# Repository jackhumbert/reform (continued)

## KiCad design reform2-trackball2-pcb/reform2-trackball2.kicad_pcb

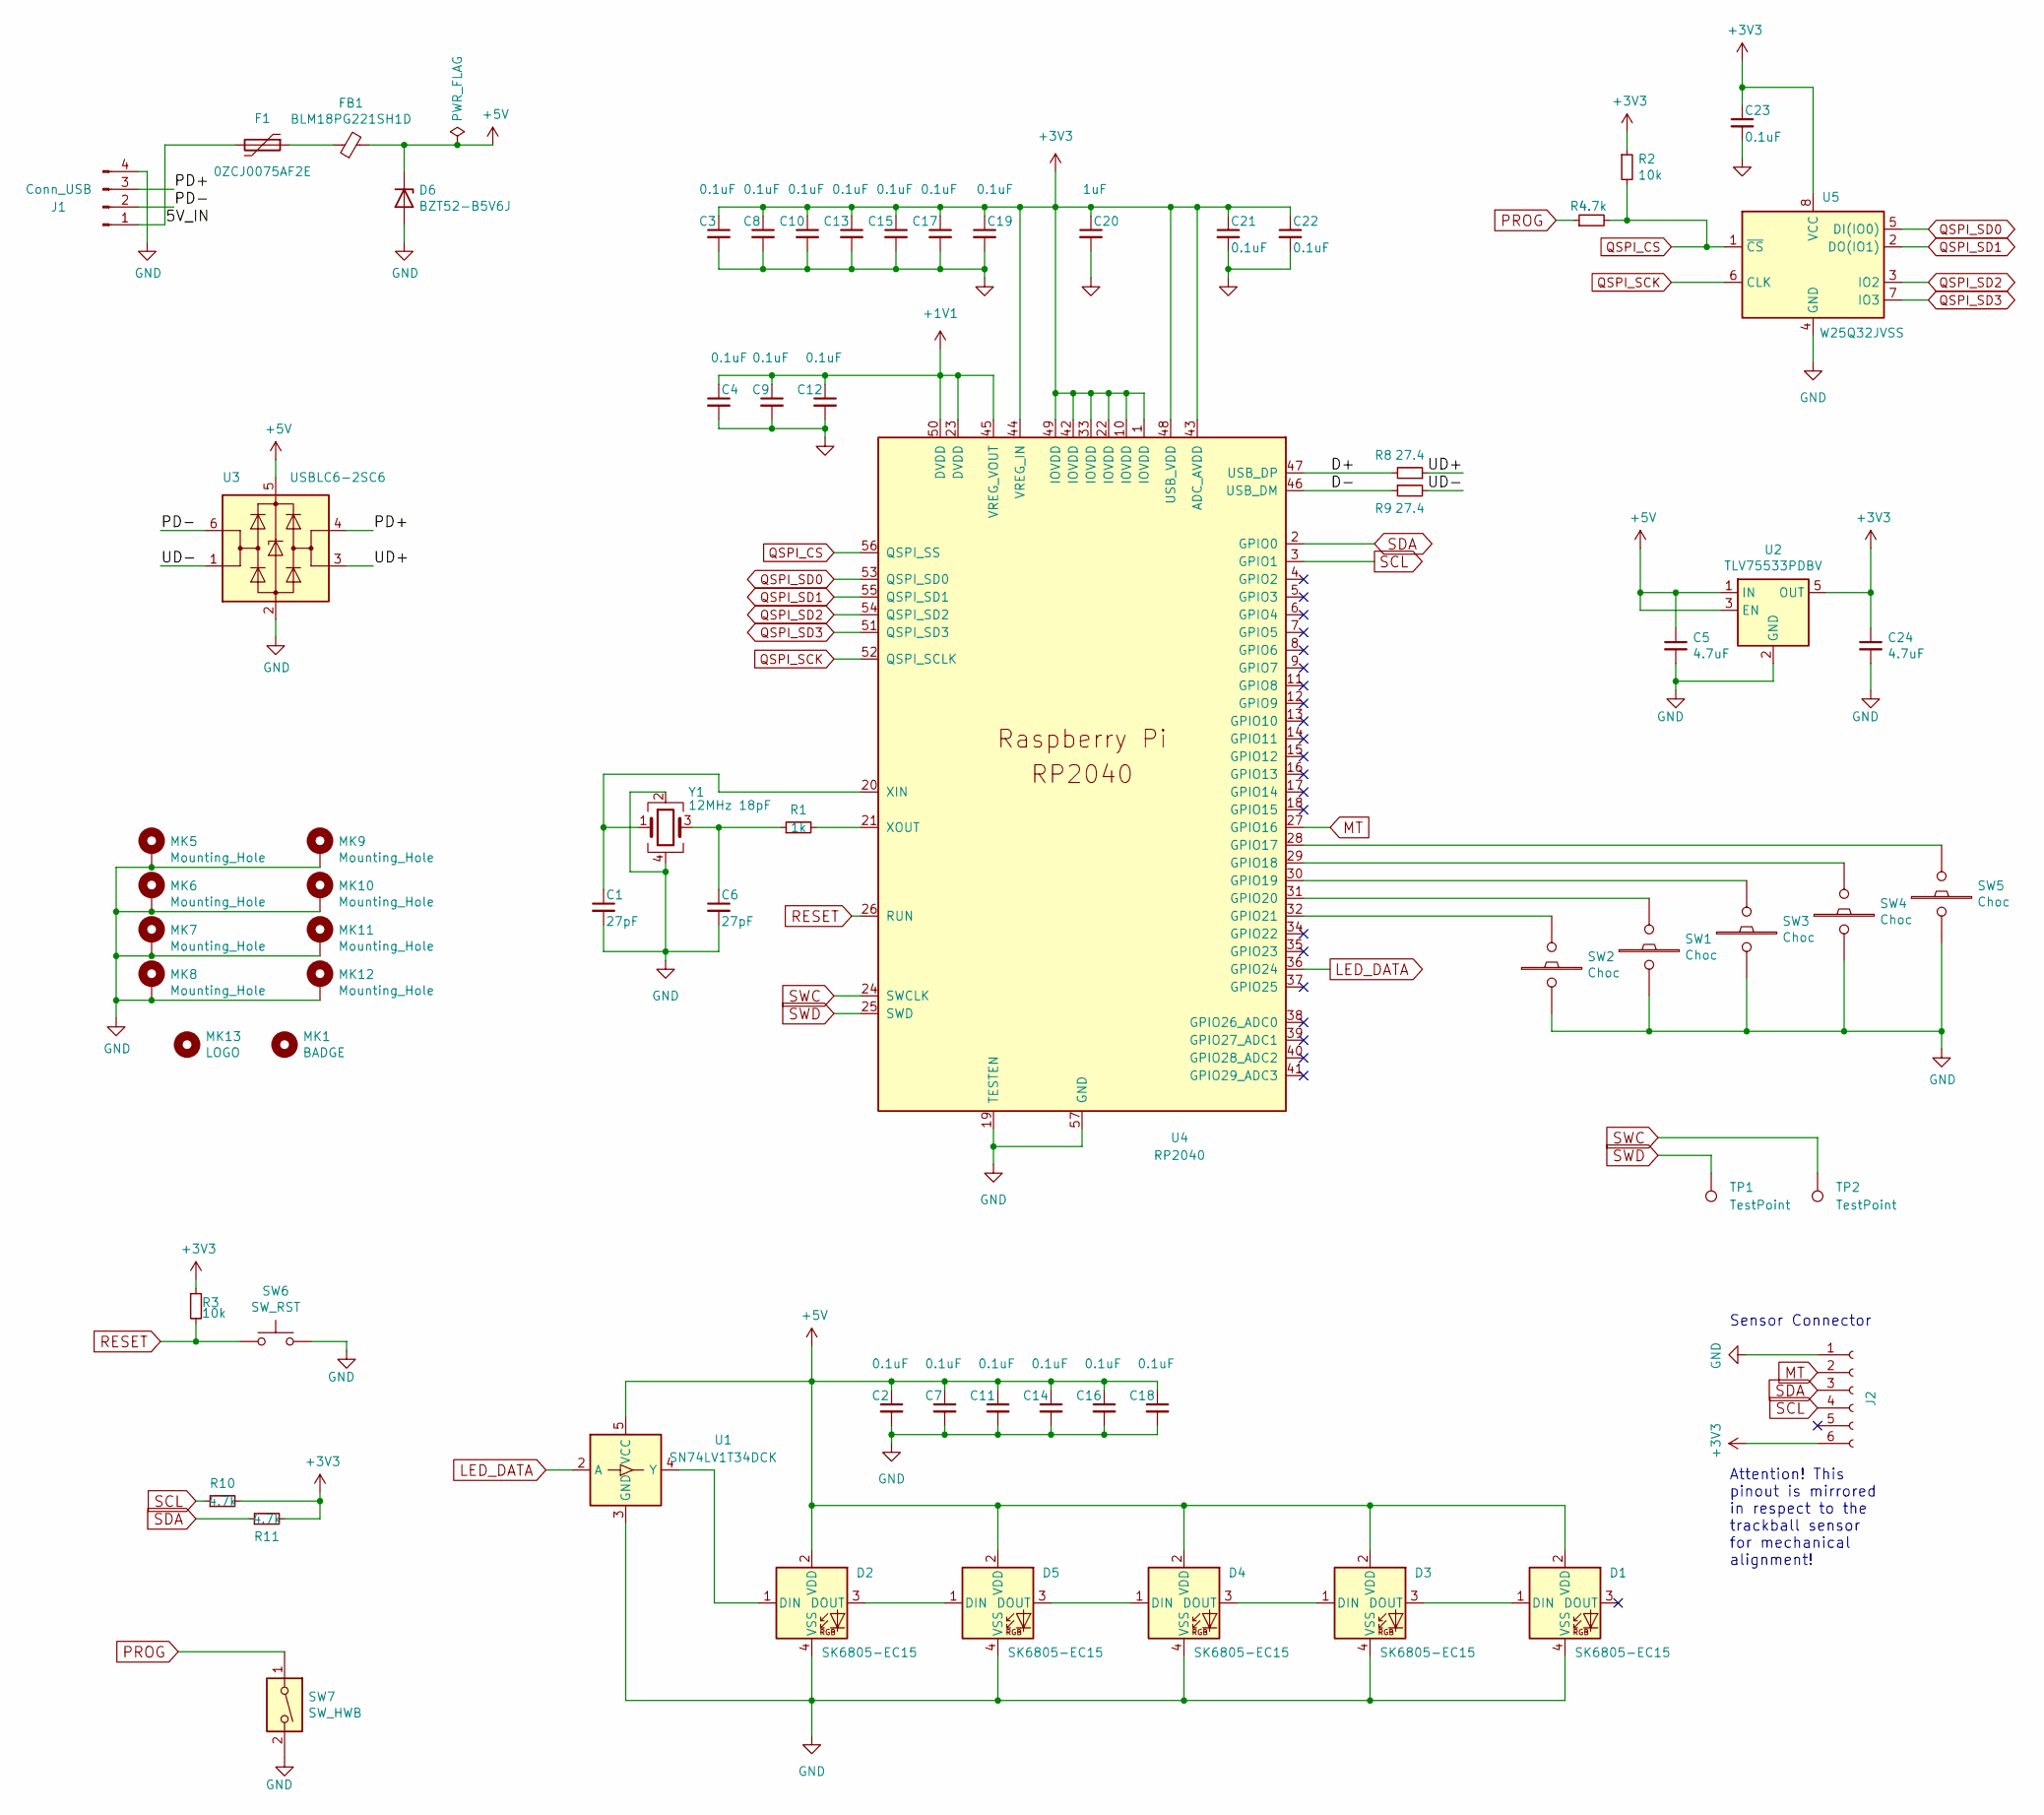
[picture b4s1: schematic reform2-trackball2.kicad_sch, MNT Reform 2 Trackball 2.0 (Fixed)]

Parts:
C1, C6: 27pF; C_0603_1608Metric; LCSC C107045
C2, C3, C4, C7, C8, C9, C10, C11, C12, C13, C14, C15, C16, C17, C18, C19, C21, C22, C23: 0.1uF; C_0603_1608Metric; LCSC C14663
C5, C24: 4.7uF; C_0603_1608Metric; LCSC C90057
C20: 1uF; C_0603_1608Metric; LCSC C14664
D1, D2, D3, D4, D5: SK6805-EC15; LCSC C2890035
D6: BZT52-B5V6J; D_SOD-123; LCSC C173406
F1: 0ZCJ0075AF2E; Fuse_1206_3216Metric_Castellated; LCSC C70082
FB1: BLM18PG221SH1D; L_0603_1608Metric; LCSC C14709
J1: Conn_USB; JST_PH_B4B-PH-K_1x04_P2.00mm_Vertical; LCSC C131334
J2: Conn_01x06_Female; Hirose_FH12-6S-0.5SH_1x06-1MP_P0.50mm_Horizontal; LCSC C202118
MK1: BADGE; mntreform-trackball-badge; LCSC DNP
MK5, MK6, MK7, MK8, MK9, MK10, MK11, MK12: Mounting_Hole; MountingHole_2.2mm_M2_Pad; LCSC DNP
MK13: LOGO; mntreform; LCSC DNP
R1: 1k; R_0603_1608Metric
R2, R3: 10k; R_0603_1608Metric; LCSC C99198
R4, R10, R11: 4.7k; R_0603_1608Metric; LCSC C105428
R8, R9: 27.4; R_0603_1608Metric; LCSC C185346
SW1, SW2, SW3, SW4, SW5: Choc; PG1350; LCSC C400231
SW6: SW_RST; Diptronics-PTLP2; LCSC C318893
SW7: SW_HWB; SW_DIP_SPSTx01_Slide_Omron_A6S-110x_W8.9mm_P2.54mm; LCSC C402914
TP1, TP2: TestPoint; TestPoint_Pad_D1.0mm; LCSC DNP
U1: SN74LV1T34DCK; SOT-353_SC-70-5; LCSC C78541
U2: TLV75533PDBV; SOT-23-5; LCSC C404027
U3: USBLC6-2SC6; SOT-23-6; LCSC C7519
U4: RP2040; RP2040-QFN-56; LCSC C2040
U5: W25Q32JVSS; SOIC-8_5.23x5.23mm_P1.27mm; LCSC C82344
Y1: 12MHz 18pF; Crystal_SMD_3225-4Pin_3.2x2.5mm; LCSC C91749

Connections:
+1V1: C4.1, C9.1, C12.1, U4.23 (DVDD), U4.45 (VREG_VOUT), U4.50 (DVDD)
/5V_IN: F1.2, J1.1
/D+: R8.2, U4.47 (USB_DP)
/D-: R9.1, U4.46 (USB_DM)
/PD+: J1.3, U3.4 (I/O2)
/PD-: J1.2, U3.6 (I/O1)
/UD+: R8.1, U3.3 (I/O2)
/UD-: R9.2, U3.1 (I/O1)
LED_DATA: U1.2 (A), U4.36 (GPIO24)
MT: J2.2, U4.27 (GPIO16)
unnamed: C1.1, U4.20 (XIN), Y1.1
unnamed: C6.1, R1.1, Y1.3
unnamed: D1.1 (DIN), D3.3 (DOUT)
unnamed: D2.1 (DIN), U1.4 (Y)
unnamed: D2.3 (DOUT), D5.1 (DIN)
unnamed: D3.1 (DIN), D4.3 (DOUT)
unnamed: D4.1 (DIN), D5.3 (DOUT)
unnamed: F1.1, FB1.1
unnamed: R1.2, U4.21 (XOUT)
unnamed: SW1.1, U4.31 (GPIO20)
unnamed: SW2.1, U4.32 (GPIO21)
unnamed: SW3.1, U4.30 (GPIO19)
unnamed: SW4.1, U4.29 (GPIO18)
unnamed: SW5.1, U4.28 (GPIO17)
PROG: R4.1, SW7.1
QSPI_CS: R2.2, R4.2, U4.56 (QSPI_SS), U5.1 (~CS)
QSPI_SCK: U4.52 (QSPI_SCLK), U5.6 (CLK)
QSPI_SD0: U4.53 (QSPI_SD0), U5.5 (DI(IO0))
QSPI_SD1: U4.55 (QSPI_SD1), U5.2 (DO(IO1))
QSPI_SD2: U4.54 (QSPI_SD2), U5.3 (IO2)
QSPI_SD3: U4.51 (QSPI_SD3), U5.7 (IO3)
RESET: R3.2, SW6.1, U4.26 (RUN)
SCL: J2.4, R10.1, U4.3 (GPIO1)
SDA: J2.3, R11.1, U4.2 (GPIO0)
SWC: TP2.1, U4.24 (SWCLK)
SWD: TP1.1, U4.25 (SWD)

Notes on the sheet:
Sensor Connector
Attention! This pinout is mirrored in respect to the trackball sensor for mechanical alignment!

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
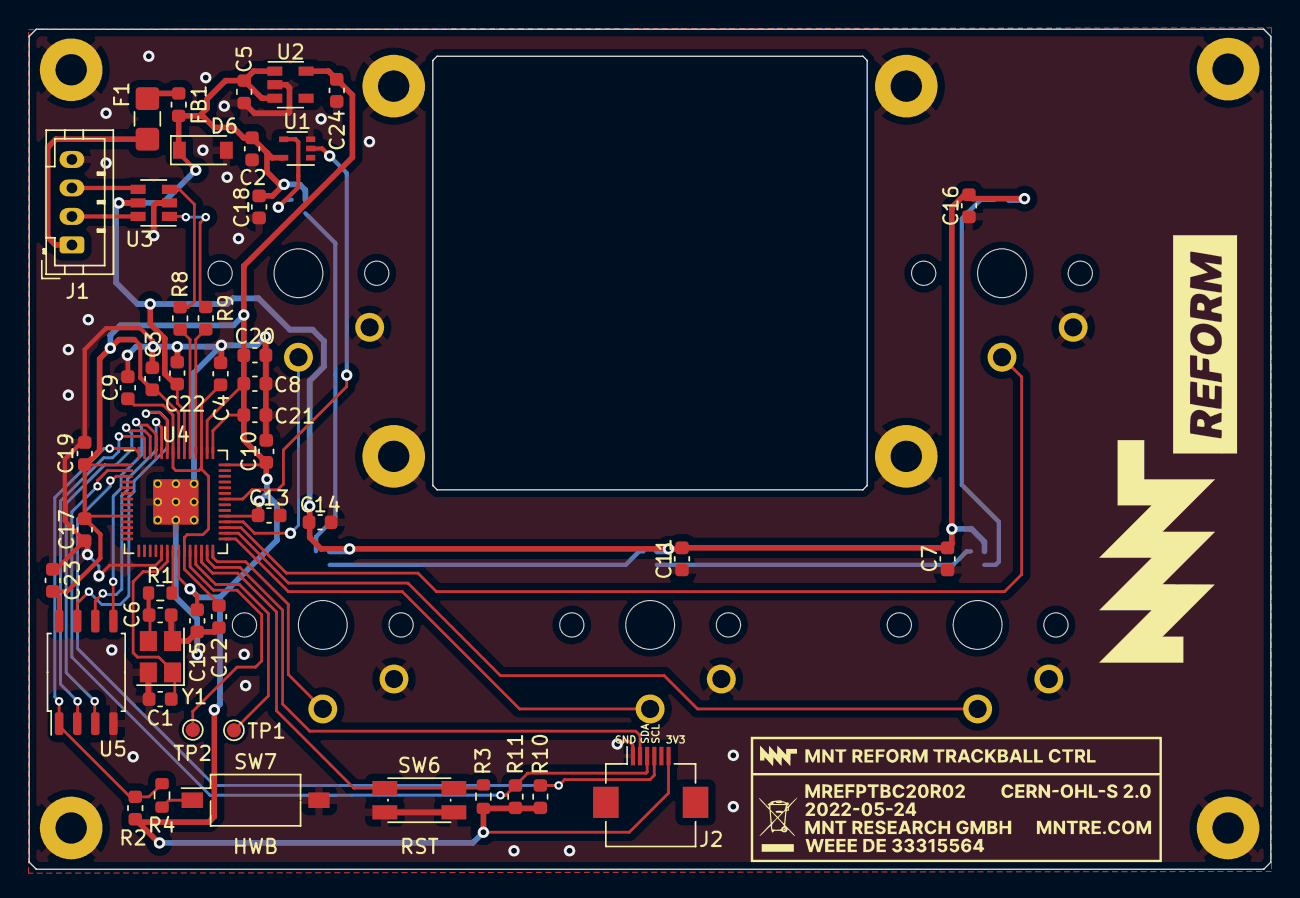
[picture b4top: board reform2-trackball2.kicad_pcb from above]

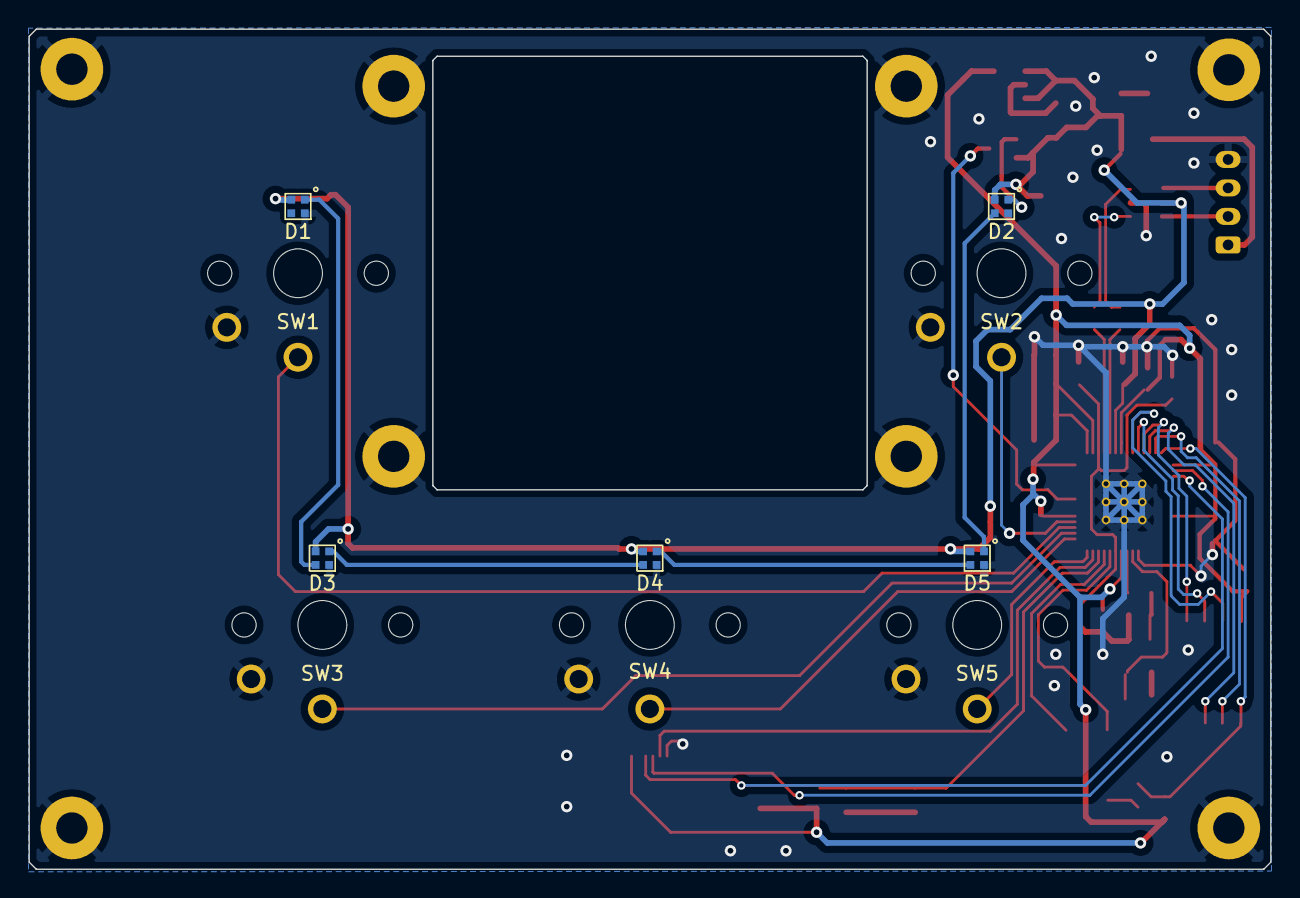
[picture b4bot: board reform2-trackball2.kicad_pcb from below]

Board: 2 copper layers, 87.2 x 59.0 mm, 67 parts (10 on the bottom side), 39 nets.

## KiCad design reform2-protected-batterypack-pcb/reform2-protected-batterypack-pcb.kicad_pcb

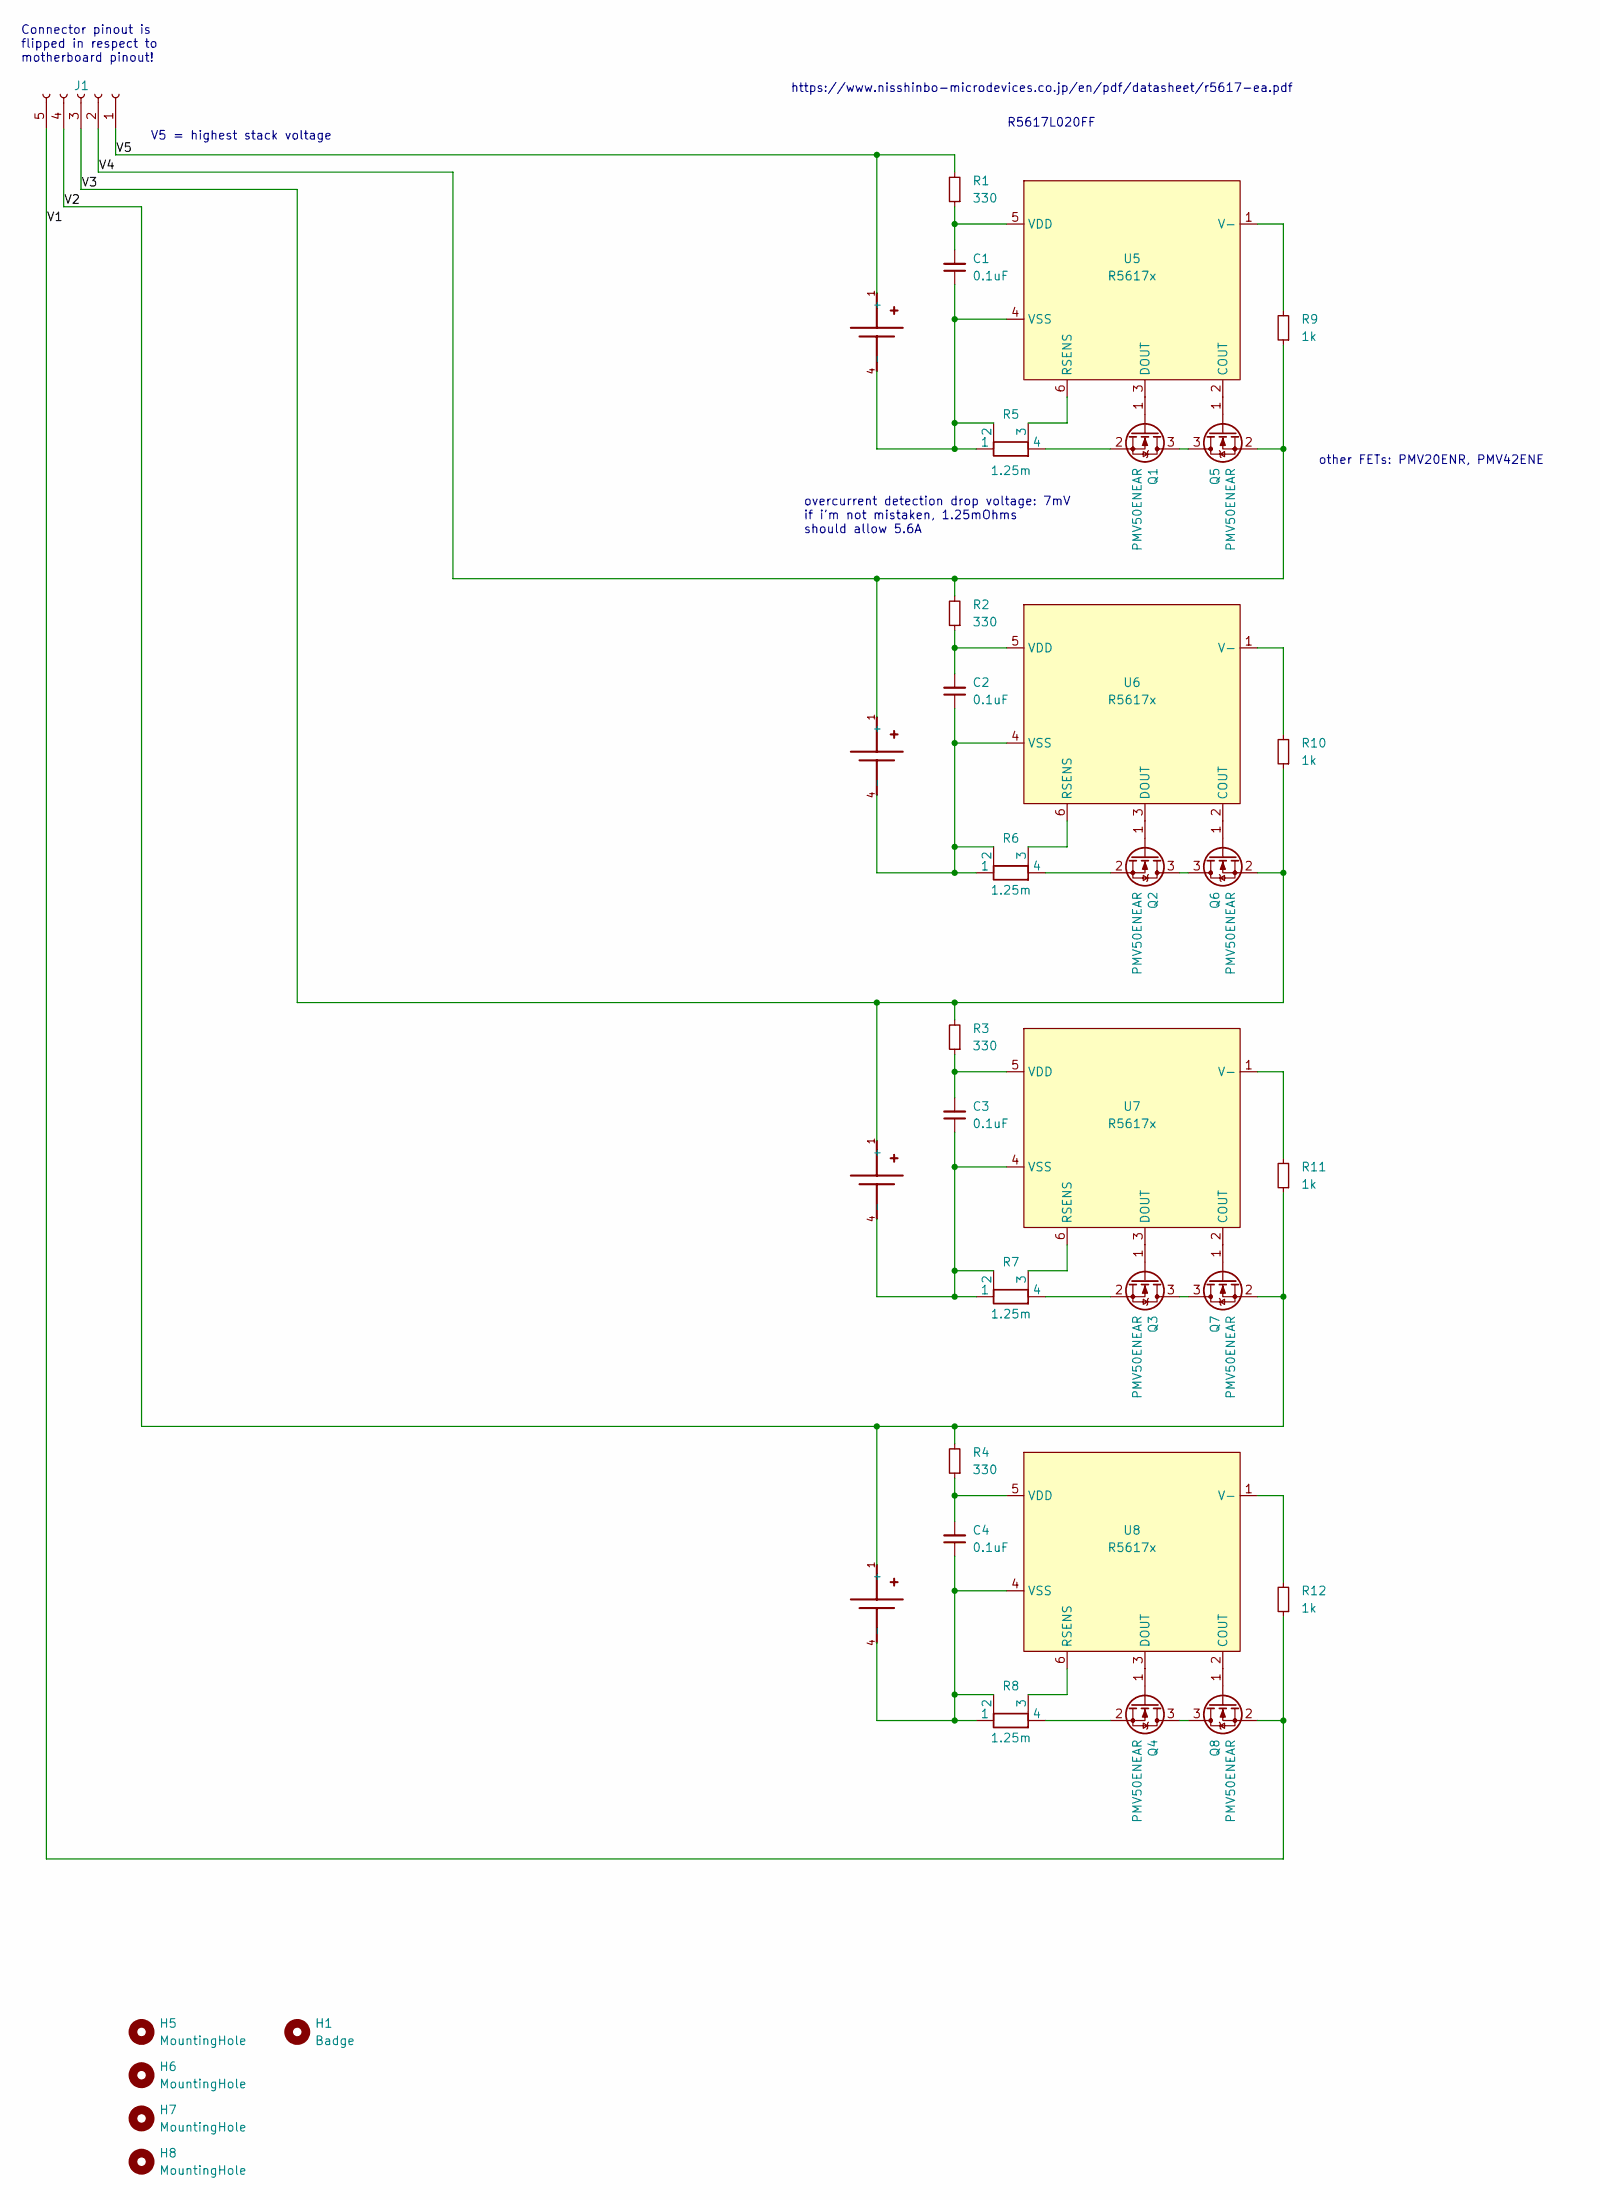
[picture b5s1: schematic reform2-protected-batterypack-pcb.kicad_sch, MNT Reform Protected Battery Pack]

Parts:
C1, C2, C3, C4: 0.1uF; C_0603_1608Metric
H1: Badge; mref-protected-batterypack-badge
H5, H6, H7, H8: MountingHole; MountingHole_2.2mm_M2
J1: Conn_01x05_Female; Molex_Pico-Lock_504050-0591_1x05-1MP_P1.50mm_Horizontal
Q1, Q2, Q3, Q4, Q5, Q6, Q7, Q8: PMV50ENEAR; SOT-23
R1, R2, R3, R4: 330; R_0603_1608Metric
R5, R6, R7, R8: 1.25m; R_1206_3216Metric_Kelvin
R9, R10, R11, R12: 1k; R_0603_1608Metric
U1, U2, U3, U4: KEYSTONE_54; Keystone54
U5, U6, U7, U8: R5617x; DFN-R5617_P0.5mm

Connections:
/V1: J1.5, Q8.2 (S), R12.1
/V2: J1.4, Q7.2 (S), R4.2, R11.1, U4.1 (+), U4.2 (+), U4.3 (+)
/V3: J1.3, Q6.2 (S), R3.2, R10.1, U3.1 (+), U3.2 (+), U3.3 (+)
/V4: J1.2, Q5.2 (S), R2.2, R9.1, U2.1 (+), U2.2 (+), U2.3 (+)
/V5: J1.1, R1.2, U1.1 (+), U1.2 (+), U1.3 (+)
unnamed: C1.1, R5.1, R5.2, U1.4 (-), U1.5 (-), U1.6 (-), U5.4 (VSS)
unnamed: C1.2, R1.1, U5.5 (VDD)
unnamed: C2.1, R6.1, R6.2, U2.4 (-), U2.5 (-), U2.6 (-), U6.4 (VSS)
unnamed: C2.2, R2.1, U6.5 (VDD)
unnamed: C3.1, R7.1, R7.2, U3.4 (-), U3.5 (-), U3.6 (-), U7.4 (VSS)
unnamed: C3.2, R3.1, U7.5 (VDD)
unnamed: C4.1, R8.1, R8.2, U4.4 (-), U4.5 (-), U4.6 (-), U8.4 (VSS)
unnamed: C4.2, R4.1, U8.5 (VDD)
unnamed: Q1.1 (G), U5.3 (DOUT)
unnamed: Q1.2 (S), R5.4
unnamed: Q1.3 (D), Q5.3 (D)
unnamed: Q2.1 (G), U6.3 (DOUT)
unnamed: Q2.2 (S), R6.4
unnamed: Q2.3 (D), Q6.3 (D)
unnamed: Q3.1 (G), U7.3 (DOUT)
unnamed: Q3.2 (S), R7.4
unnamed: Q3.3 (D), Q7.3 (D)
unnamed: Q4.1 (G), U8.3 (DOUT)
unnamed: Q4.2 (S), R8.4
unnamed: Q4.3 (D), Q8.3 (D)
unnamed: Q5.1 (G), U5.2 (COUT)
unnamed: Q6.1 (G), U6.2 (COUT)
unnamed: Q7.1 (G), U7.2 (COUT)
unnamed: Q8.1 (G), U8.2 (COUT)
unnamed: R6.3, U6.6 (RSENS)
unnamed: R7.3, U7.6 (RSENS)
unnamed: R8.3, U8.6 (RSENS)
unnamed: R9.2, U5.1 (V-)
unnamed: R10.2, U6.1 (V-)
unnamed: R11.2, U7.1 (V-)
unnamed: R12.2, U8.1 (V-)
unnamed: R5.3, U5.6 (RSENS)

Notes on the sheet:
other FETs: PMV20ENR, PMV42ENE
overcurrent detection drop voltage: 7mV if i'm not mistaken, 1.25mOhms should allow 5.6A
R5617L020FF
https://www.nisshinbo-microdevices.co.jp/en/pdf/datasheet/r5617-ea.pdf
V5 = highest stack voltage
Connector pinout is flipped in respect to motherboard pinout!

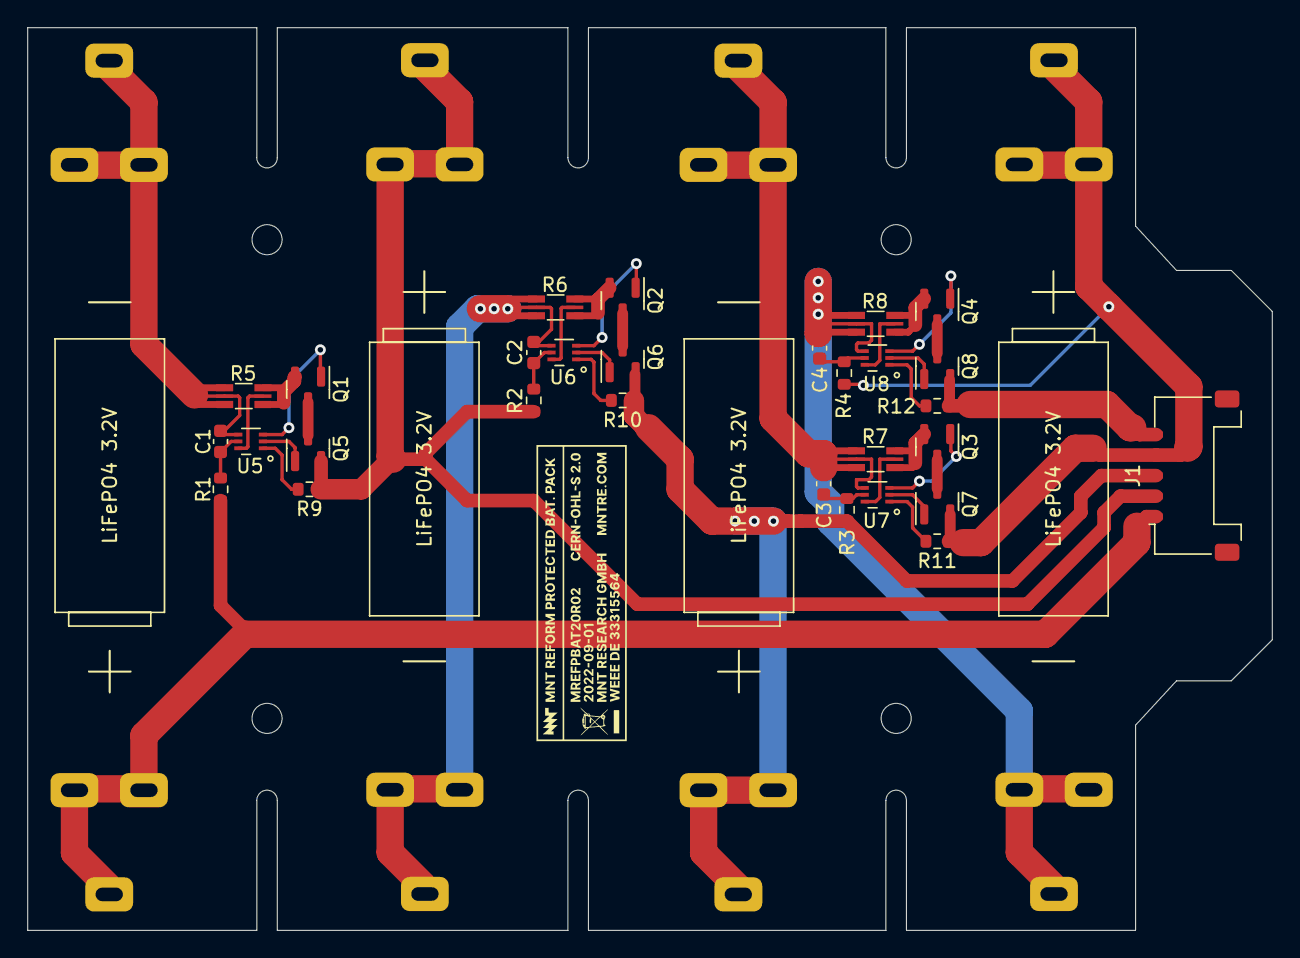
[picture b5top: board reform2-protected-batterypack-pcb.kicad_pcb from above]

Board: 2 copper layers, 91.0 x 66.0 mm, 38 parts (0 on the bottom side), 37 nets.

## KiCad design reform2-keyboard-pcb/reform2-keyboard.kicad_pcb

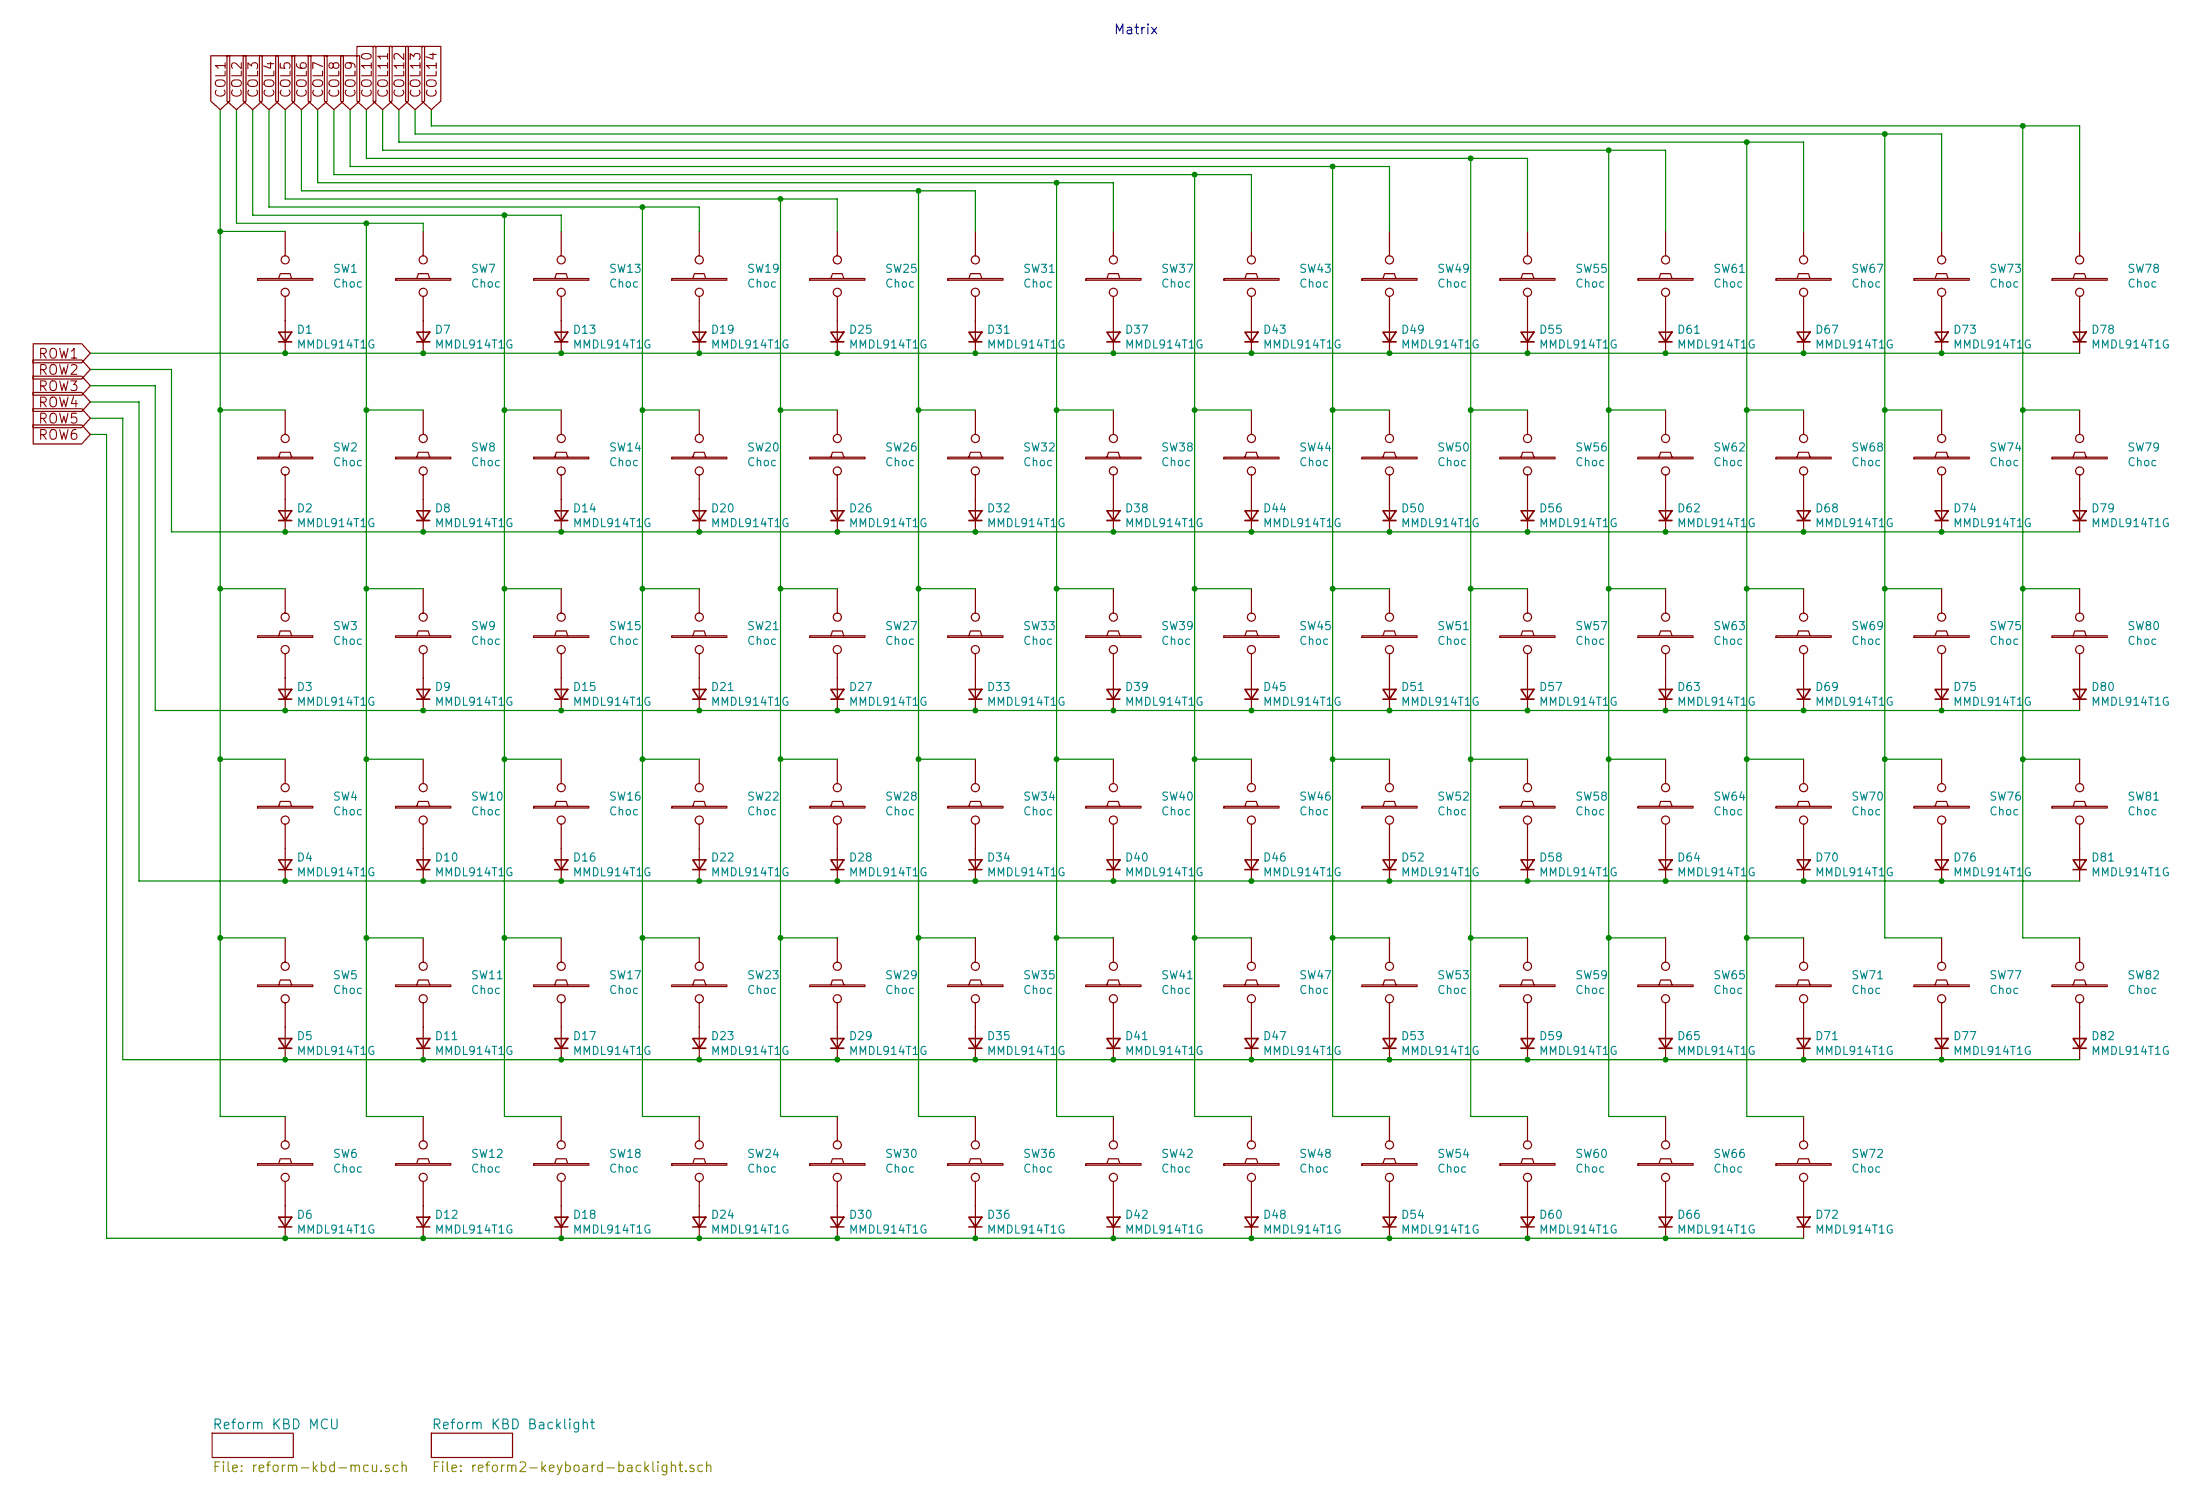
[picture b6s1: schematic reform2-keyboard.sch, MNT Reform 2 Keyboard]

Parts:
D1, D2, D3, D4, D5, D6, D7, D8, D9, D10, D11, D12, D13, D14, D15, D16, D17, D18, D19, D20, D21, D22, D23, D24, D25, D26, D27, D28, D29, D30, D31, D32, D33, D34, D35, D36, D37, D38, D39, D40, D41, D42, D43, D44, D45, D46, D47, D48, D49, D50, D51, D52, D53, D54, D55, D56, D57, D58, D59, D60, D61, D62, D63, D64, D65, D66, D67, D68, D69, D70, D71, D72, D73, D74, D75, D76, D77, D78, D79, D80, D81, D82: MMDL914T1G; D_0603_1608Metric_Pad1.05x0.95mm_HandSolder
SW1, SW2, SW3, SW4, SW5, SW6, SW7, SW8, SW9, SW10, SW11, SW12, SW13, SW14, SW15, SW16, SW17, SW18, SW19, SW20, SW21, SW22, SW23, SW24, SW25, SW26, SW27, SW28, SW29, SW30, SW31, SW32, SW33, SW34, SW35, SW36, SW37, SW38, SW39, SW40, SW41, SW42, SW43, SW44, SW45, SW46, SW47, SW48, SW49, SW50, SW51, SW52, SW53, SW54, SW55, SW56, SW57, SW58, SW59, SW60, SW61, SW62, SW63, SW64, SW65, SW66, SW67, SW68, SW69, SW70, SW71, SW72, SW73, SW74, SW75, SW76, SW77, SW78, SW79, SW80, SW81, SW82: Choc; PG1350

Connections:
COL1: SW1.1, SW2.1, SW3.1, SW4.1, SW5.1, SW6.1; also elsewhere on the board
COL2: SW7.1, SW8.1, SW9.1, SW10.1, SW11.1, SW12.1; also elsewhere on the board
COL3: SW13.1, SW14.1, SW15.1, SW16.1, SW17.1, SW18.1; also elsewhere on the board
COL4: SW19.1, SW20.1, SW21.1, SW22.1, SW23.1, SW24.1; also elsewhere on the board
COL5: SW25.1, SW26.1, SW27.1, SW28.1, SW29.1, SW30.1; also elsewhere on the board
COL6: SW31.1, SW32.1, SW33.1, SW34.1, SW35.1, SW36.1; also elsewhere on the board
COL7: SW37.1, SW38.1, SW39.1, SW40.1, SW41.1, SW42.1; also elsewhere on the board
COL8: SW43.1, SW44.1, SW45.1, SW46.1, SW47.1, SW48.1; also elsewhere on the board
COL9: SW49.1, SW50.1, SW51.1, SW52.1, SW53.1, SW54.1; also elsewhere on the board
COL10: SW55.1, SW56.1, SW57.1, SW58.1, SW59.1, SW60.1; also elsewhere on the board
COL11: SW61.1, SW62.1, SW63.1, SW64.1, SW65.1, SW66.1; also elsewhere on the board
COL12: SW67.1, SW68.1, SW69.1, SW70.1, SW71.1, SW72.1; also elsewhere on the board
COL13: SW73.1, SW74.1, SW75.1, SW76.1, SW77.1; also elsewhere on the board
COL14: SW78.1, SW79.1, SW80.1, SW81.1, SW82.1; also elsewhere on the board
unnamed: D1.2 (A), SW1.2
unnamed: D2.2 (A), SW2.2
unnamed: D3.2 (A), SW3.2
unnamed: D4.2 (A), SW4.2
unnamed: D5.2 (A), SW5.2
unnamed: D6.2 (A), SW6.2
unnamed: D7.2 (A), SW7.2
unnamed: D8.2 (A), SW8.2
unnamed: D9.2 (A), SW9.2
unnamed: D10.2 (A), SW10.2
unnamed: D11.2 (A), SW11.2
unnamed: D12.2 (A), SW12.2
unnamed: D13.2 (A), SW13.2
unnamed: D14.2 (A), SW14.2
unnamed: D15.2 (A), SW15.2
unnamed: D16.2 (A), SW16.2
unnamed: D17.2 (A), SW17.2
unnamed: D18.2 (A), SW18.2
unnamed: D19.2 (A), SW19.2
unnamed: D20.2 (A), SW20.2
unnamed: D21.2 (A), SW21.2
unnamed: D22.2 (A), SW22.2
unnamed: D23.2 (A), SW23.2
unnamed: D24.2 (A), SW24.2
unnamed: D25.2 (A), SW25.2
unnamed: D26.2 (A), SW26.2
unnamed: D27.2 (A), SW27.2
unnamed: D28.2 (A), SW28.2
unnamed: D29.2 (A), SW29.2
unnamed: D30.2 (A), SW30.2
unnamed: D31.2 (A), SW31.2
unnamed: D32.2 (A), SW32.2
unnamed: D33.2 (A), SW33.2
unnamed: D34.2 (A), SW34.2
unnamed: D35.2 (A), SW35.2
unnamed: D36.2 (A), SW36.2
unnamed: D37.2 (A), SW37.2
unnamed: D38.2 (A), SW38.2
unnamed: D39.2 (A), SW39.2
unnamed: D40.2 (A), SW40.2
unnamed: D41.2 (A), SW41.2
unnamed: D42.2 (A), SW42.2
unnamed: D43.2 (A), SW43.2
unnamed: D44.2 (A), SW44.2
unnamed: D45.2 (A), SW45.2
unnamed: D46.2 (A), SW46.2
unnamed: D47.2 (A), SW47.2
unnamed: D48.2 (A), SW48.2
unnamed: D49.2 (A), SW49.2
unnamed: D50.2 (A), SW50.2
unnamed: D51.2 (A), SW51.2
unnamed: D52.2 (A), SW52.2
unnamed: D53.2 (A), SW53.2
unnamed: D54.2 (A), SW54.2
unnamed: D55.2 (A), SW55.2
unnamed: D56.2 (A), SW56.2
unnamed: D57.2 (A), SW57.2
unnamed: D58.2 (A), SW58.2
unnamed: D59.2 (A), SW59.2
unnamed: D60.2 (A), SW60.2
unnamed: D61.2 (A), SW61.2
unnamed: D62.2 (A), SW62.2
unnamed: D63.2 (A), SW63.2
unnamed: D64.2 (A), SW64.2
unnamed: D65.2 (A), SW65.2
unnamed: D66.2 (A), SW66.2
unnamed: D67.2 (A), SW67.2
unnamed: D68.2 (A), SW68.2
unnamed: D69.2 (A), SW69.2
unnamed: D70.2 (A), SW70.2
unnamed: D71.2 (A), SW71.2
unnamed: D72.2 (A), SW72.2
unnamed: D73.2 (A), SW73.2
unnamed: D74.2 (A), SW74.2
unnamed: D75.2 (A), SW75.2
unnamed: D76.2 (A), SW76.2
unnamed: D77.2 (A), SW77.2
unnamed: D78.2 (A), SW78.2
unnamed: D79.2 (A), SW79.2
unnamed: D80.2 (A), SW80.2
unnamed: D81.2 (A), SW81.2
unnamed: D82.2 (A), SW82.2
ROW1: D1.1 (K), D7.1 (K), D13.1 (K), D19.1 (K), D25.1 (K), D31.1 (K), D37.1 (K), D43.1 (K), D49.1 (K), D55.1 (K), D61.1 (K), D67.1 (K), D73.1 (K), D78.1 (K); also elsewhere on the board
ROW2: D2.1 (K), D8.1 (K), D14.1 (K), D20.1 (K), D26.1 (K), D32.1 (K), D38.1 (K), D44.1 (K), D50.1 (K), D56.1 (K), D62.1 (K), D68.1 (K), D74.1 (K), D79.1 (K); also elsewhere on the board
ROW3: D3.1 (K), D9.1 (K), D15.1 (K), D21.1 (K), D27.1 (K), D33.1 (K), D39.1 (K), D45.1 (K), D51.1 (K), D57.1 (K), D63.1 (K), D69.1 (K), D75.1 (K), D80.1 (K); also elsewhere on the board
ROW4: D4.1 (K), D10.1 (K), D16.1 (K), D22.1 (K), D28.1 (K), D34.1 (K), D40.1 (K), D46.1 (K), D52.1 (K), D58.1 (K), D64.1 (K), D70.1 (K), D76.1 (K), D81.1 (K); also elsewhere on the board
ROW5: D5.1 (K), D11.1 (K), D17.1 (K), D23.1 (K), D29.1 (K), D35.1 (K), D41.1 (K), D47.1 (K), D53.1 (K), D59.1 (K), D65.1 (K), D71.1 (K), D77.1 (K), D82.1 (K); also elsewhere on the board
ROW6: D6.1 (K), D12.1 (K), D18.1 (K), D24.1 (K), D30.1 (K), D36.1 (K), D42.1 (K), D48.1 (K), D54.1 (K), D60.1 (K), D66.1 (K), D72.1 (K); also elsewhere on the board

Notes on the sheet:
Matrix
